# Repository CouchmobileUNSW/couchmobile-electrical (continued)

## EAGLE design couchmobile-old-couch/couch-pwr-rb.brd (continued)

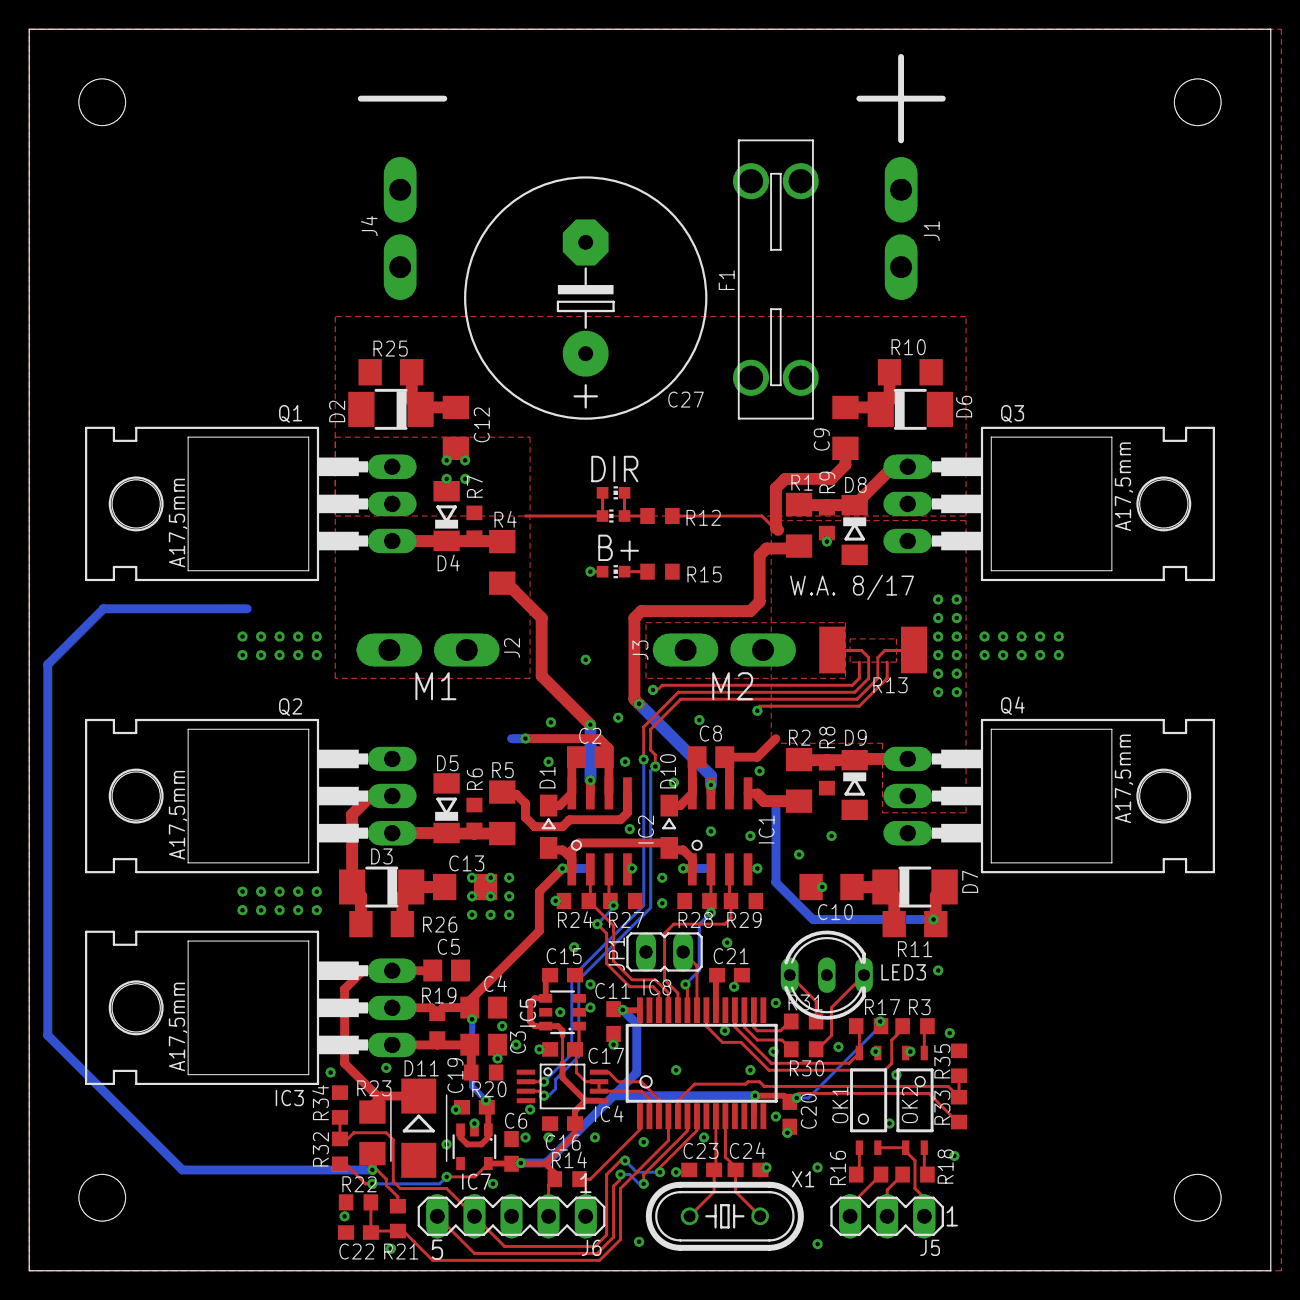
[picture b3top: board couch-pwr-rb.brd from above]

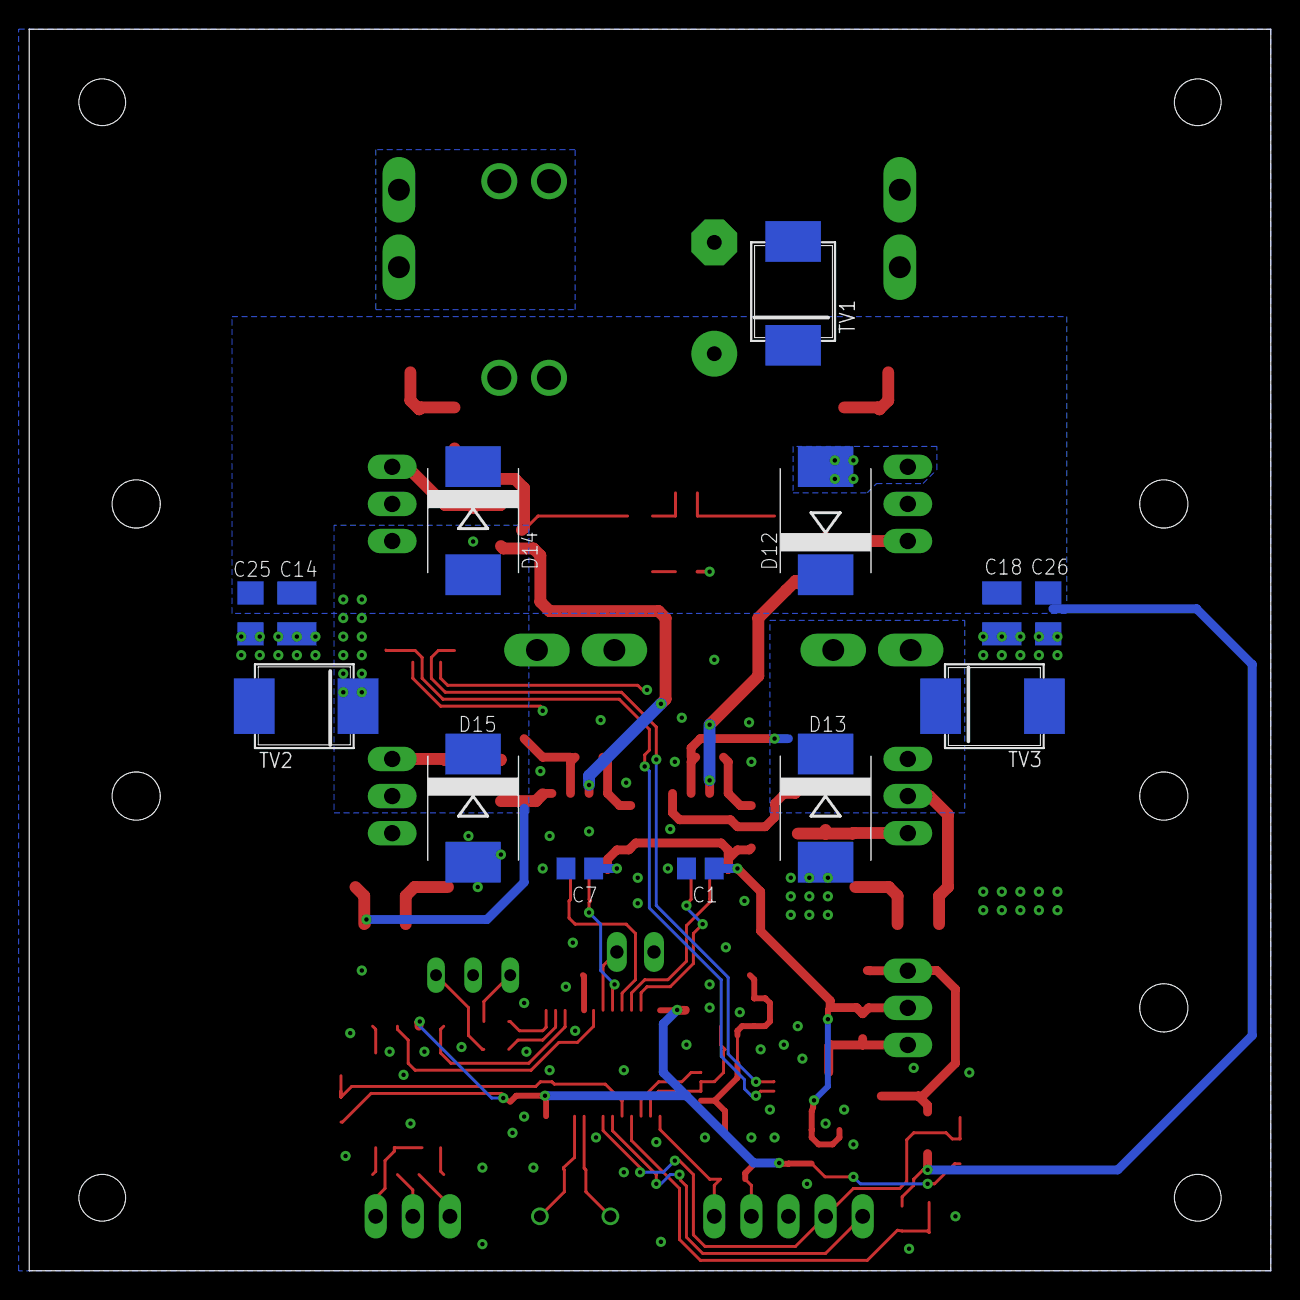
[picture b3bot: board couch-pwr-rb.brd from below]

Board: 2 copper layers, 85.0 x 85.0 mm, 106 parts (13 on the bottom side), 53 nets.

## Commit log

2019-08-04 First commit. Sending up almost finished schematic of control module.
2019-08-04 Finished nano gpio
2019-08-05 Finished wiring up schematic; DRC passed. ALso added in the AND gates
2019-08-05 Laid out the LEDs and switches
2019-08-06 Made and added so8 package for pfet
2019-08-06 Changed solder to mask clearance to 0.05mm. Wired up half the gpio for nano
2019-08-06 Wired up a lot of the busses.
2019-08-06 Added 5v to 3.3v line converters.
2019-08-07 Laid out most lines except ground
2019-08-07 Poured ground and did DRC. Fixed all markers.
2019-08-07 Changed some resistor values. Generated BOM.
2019-08-26 Finished rev1 of board
2019-08-26 Added in label to control panel
2019-08-27 Adding the couch control panel
2019-08-27 finished v0 of control pad pcb
2019-08-29 Updated labels on pcb revision 3
2019-09-22 Create LICENSE
